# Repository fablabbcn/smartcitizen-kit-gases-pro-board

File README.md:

# Smart Citizen Kit 2.0 Gases Pro Board 

### The core firmware (C++)

The technology used:

* Arduino Zero Core
* Platformio

#### Uploading the firmware to the board

After clonning the repository:

1. In folder ./firmware run:

  * `pio run`

2. This step will **take a while**. Once it finished plug the board over USB and run:

  * `pio run -t upload`

## Documentation

Full documentation under development. Follow the [forum](https://forum.smartcitizen.me/) and [twitter](https://twitter.com/SmartCitizenKit) for updates.

## Related Smart Citizen repositories

* Smart Citizen Kit 2.0 [github.com/fablabbcn/smartcitizen-kit-20](https://github.com/fablabbcn/smartcitizen-kit-20)
* Platform Core API [github.com/fablabbcn/smartcitizen-api](https://github.com/fablabbcn/smartcitizen-api)
* Platform Web [github.com/fablabbcn/smartcitizen-web](https://github.com/fablabbcn/smartcitizen-web)
* Platform Onboarding [github.com/fablabbcn/smartcitizen-onboarding-app](https://github.com/fablabbcn/smartcitizen-onboarding-app)
* Kit Enclosures [github.com/fablabbcn/smartcitizen-enclosures](https://github.com/fablabbcn/smartcitizen-enclosures)
* Useful software resources for communities [github.com/fablabbcn/smartcitizen-toolkit](https://github.com/fablabbcn/smartcitizen-toolkit)

## License

All the software unless stated is released under [GNU GPL v3.0](https://github.com/fablabbcn/smartcitizen-kit-20/blob/master/LICENSE) and the hardware design files under [CERN OHL v1.2](https://github.com/fablabbcn/smartcitizen-kit-20/blob/master/hardware/LICENSE)

## Credits

Smart Citizen Team 2012-18

## Funding

This work has received funding from the European Union's Horizon 2020 research and innovation program under the grant agreement [No. 689954](https://cordis.europa.eu/project/rcn/202639_en.html)

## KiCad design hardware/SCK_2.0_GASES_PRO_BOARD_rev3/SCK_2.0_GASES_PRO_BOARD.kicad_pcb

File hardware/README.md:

Smart Citizen Kit 2.0 PM Board Hardware
=======================================

This folder contains the KiCad design files for the Smart Citizen Kit 2.0 PM Board

## Folders

* **SCK_2.0_GASES_PRO_BOARD_rev3** The SCK Gases Pro Alphasense Driver Board
* **SCK_2.0_GASES_PRO_BOARD_TEST_UTIL_rev2** The SCK Gases Pro Calibration and Test Util

## License

All the software is released under [GNU GPL v3.0](https://github.com/fablabbcn/smartcitizen-kit-20/blob/master/LICENSE) and the hardware design files under [CERN OHL v1.2](https://github.com/fablabbcn/smartcitizen-kit-20/blob/master/hardware/LICENSE)

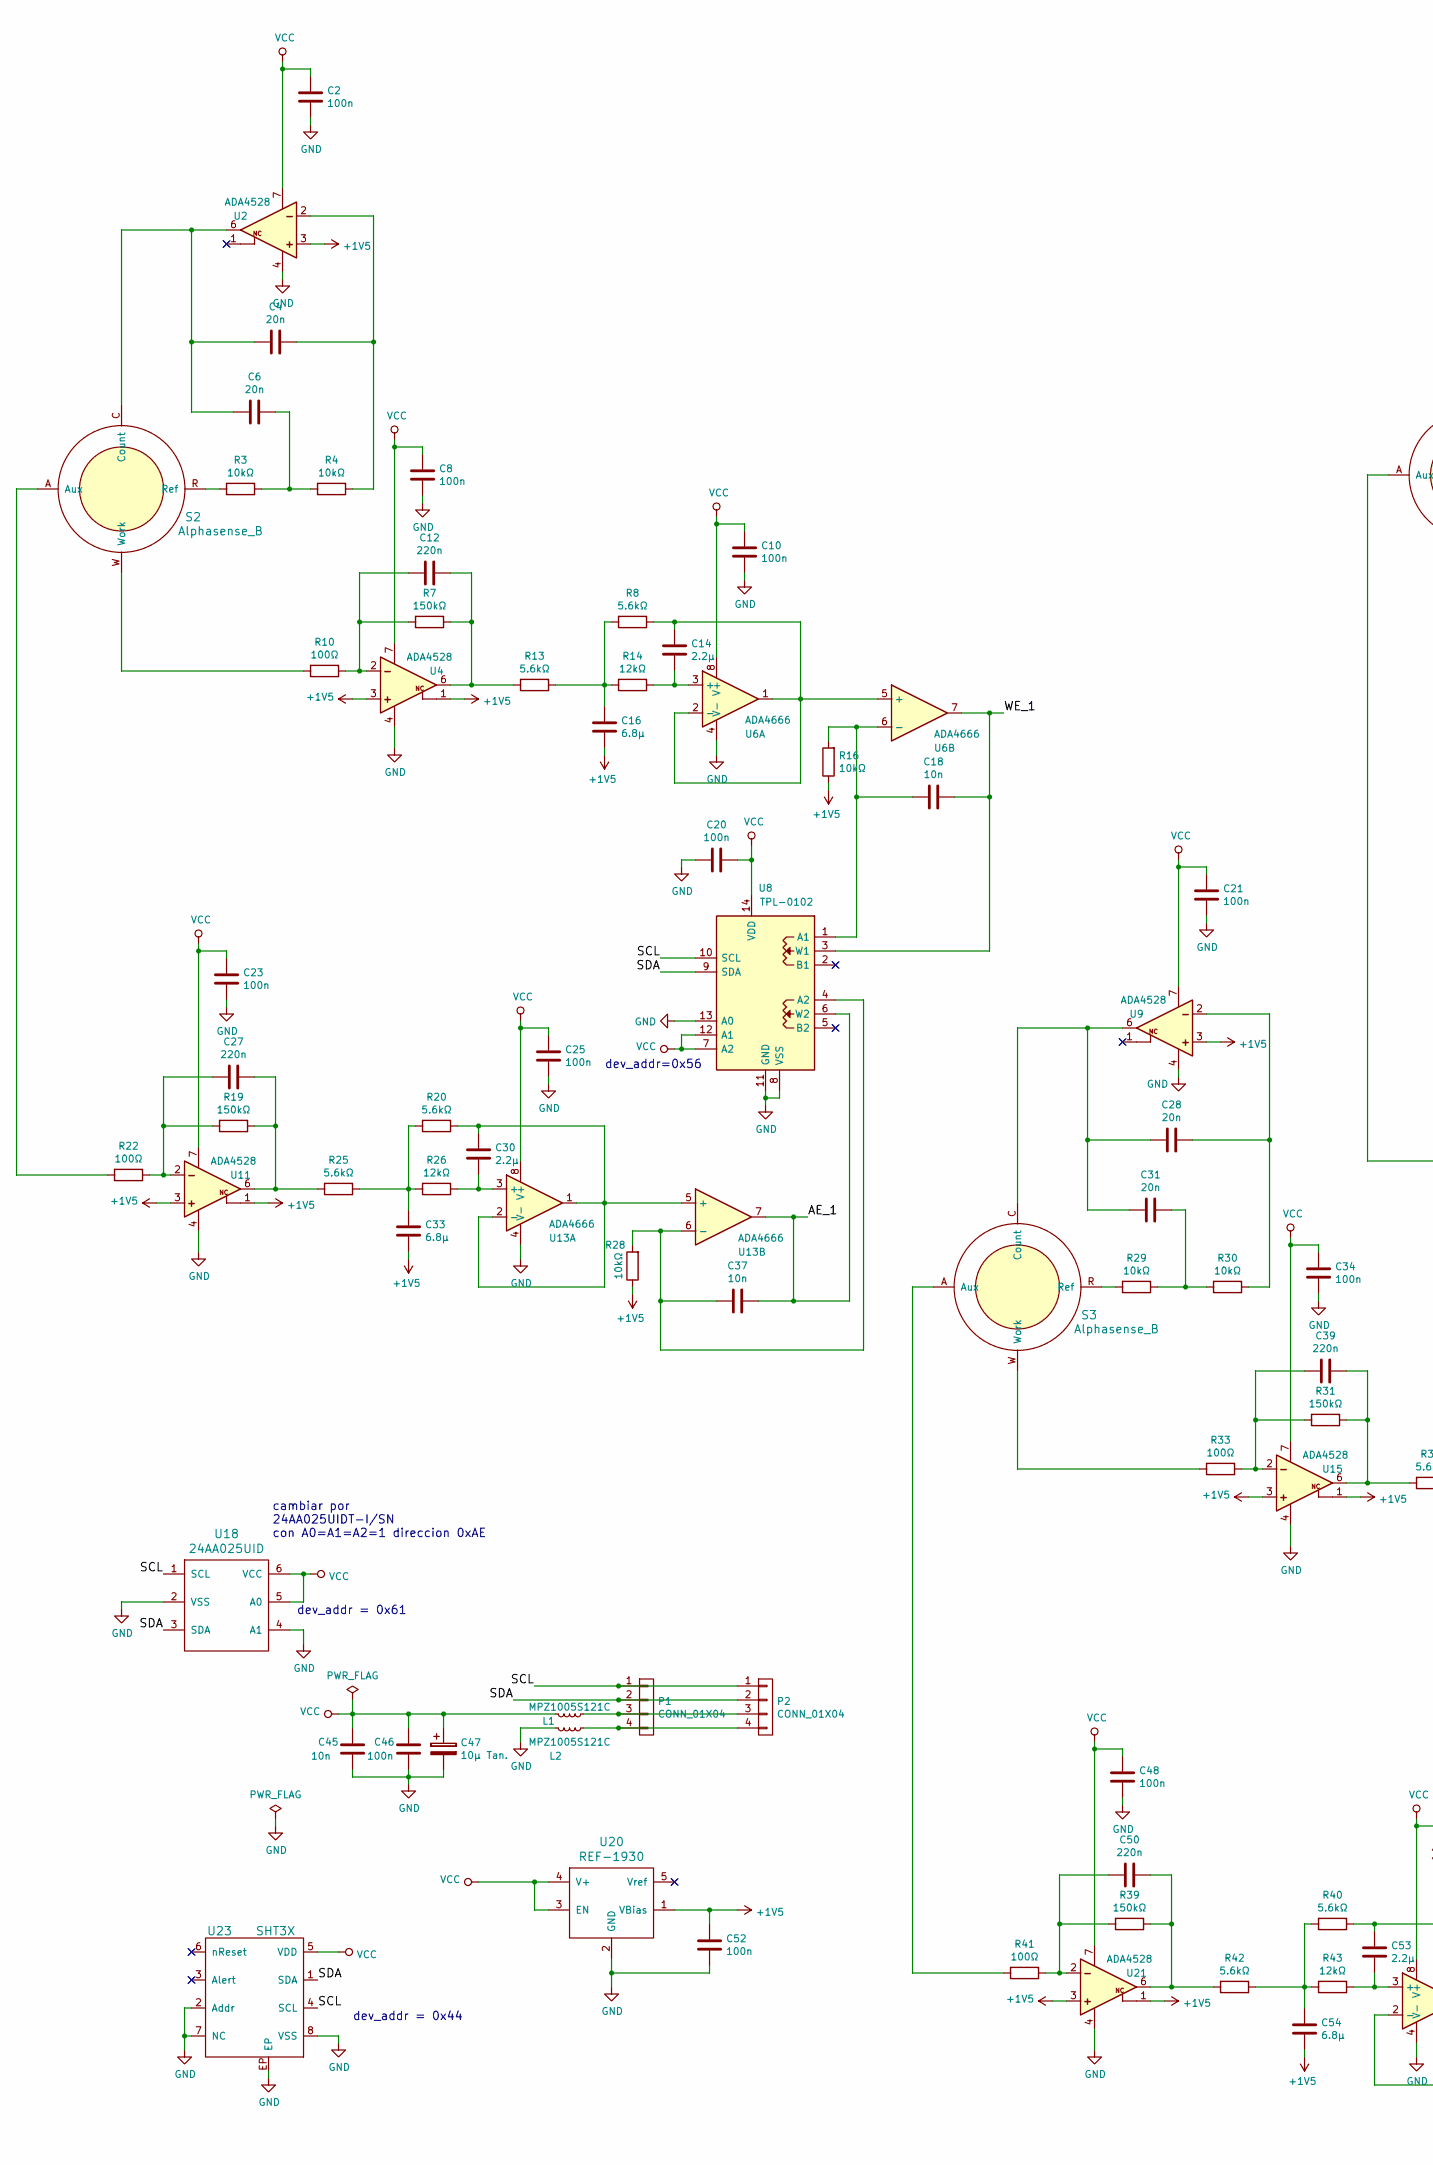
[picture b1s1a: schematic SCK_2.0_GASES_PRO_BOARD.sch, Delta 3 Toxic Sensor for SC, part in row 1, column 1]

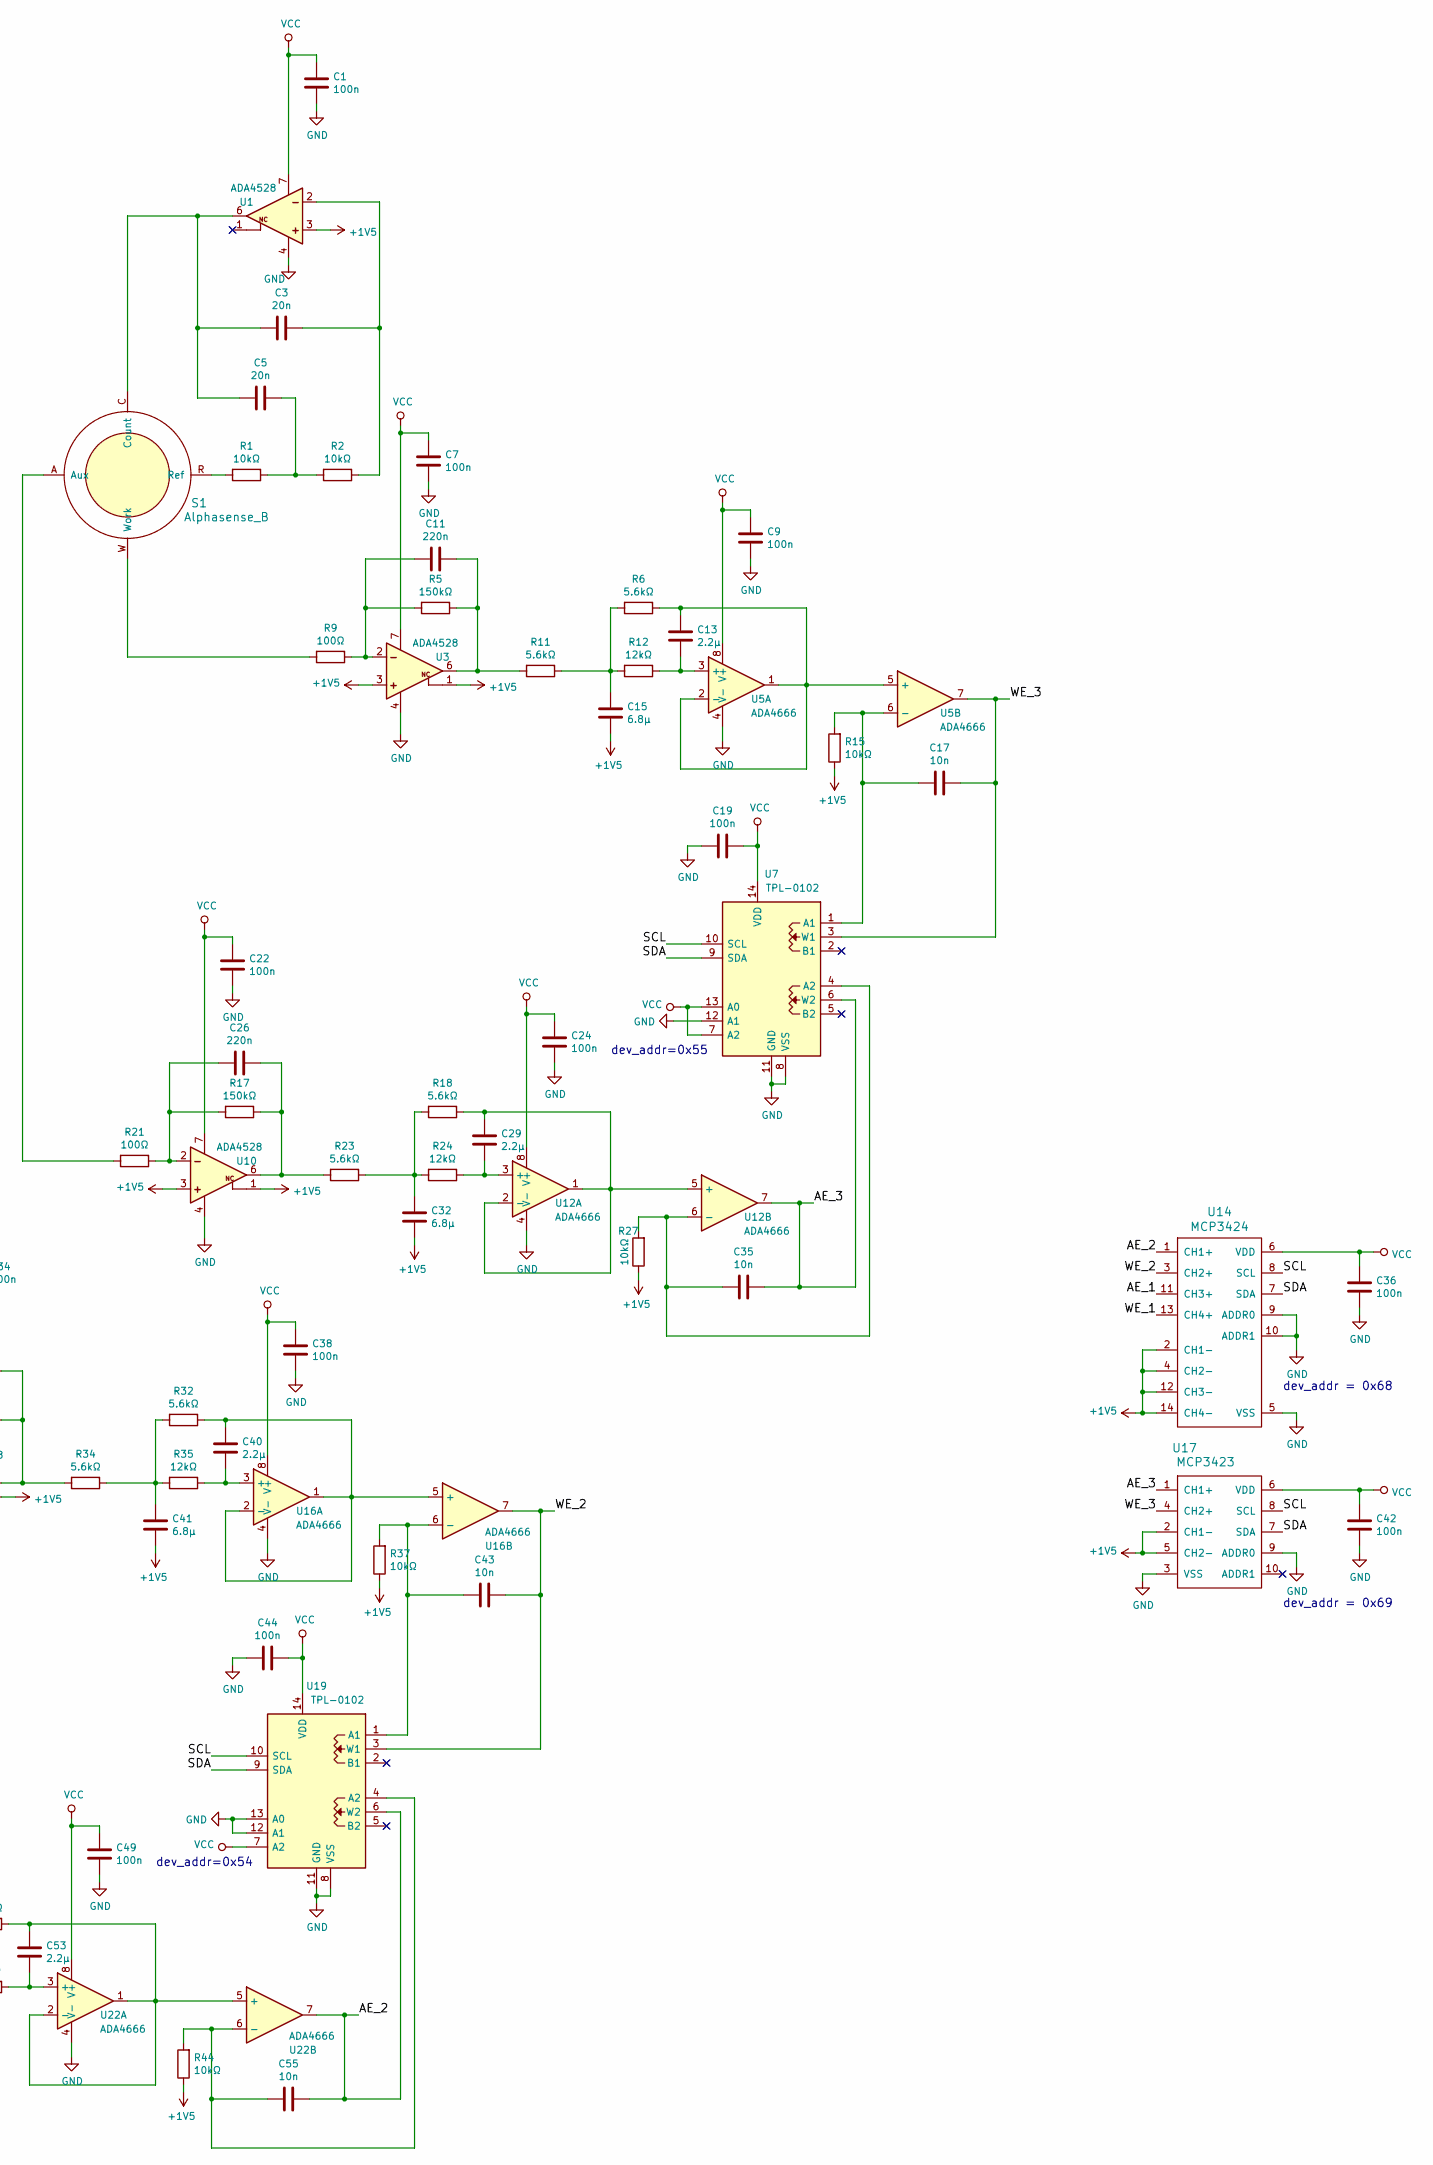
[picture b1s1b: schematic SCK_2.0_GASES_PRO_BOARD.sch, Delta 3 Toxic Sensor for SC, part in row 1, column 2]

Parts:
C1, C2, C7, C8, C9, C10, C19, C20, C21, C22, C23, C24, C25, C34, C36, C38, C42, C44, C46, C48, C49, C52: 100n; C_0603
C3, C4, C5, C6, C28, C31: 20n; C_0603
C11, C12, C26, C27, C39, C50: 220n; C_0603
C13, C14, C29, C30, C40, C53: 2.2µ; C_0603
C15, C16, C32, C33, C41, C54: 6.8µ; C_0603
C17, C18, C35, C37, C43, C45, C55: 10n; C_0603
C47: 10µ Tan.; CP_Tantalum_Case-A_EIA-3216-18_Reflow
L1, L2: MPZ1005S121C; R_0402
P1, P2: CONN_01X04; HW4-SMD-2.0
R1, R2, R3, R4, R15, R16, R27, R28, R29, R30, R37, R44: 10kΩ; R_0603
R5, R7, R17, R19, R31, R39: 150kΩ; R_0603
R6, R8, R11, R13, R18, R20, R23, R25, R32, R34, R40, R42: 5.6kΩ; R_0603
R9, R10, R21, R22, R33, R41: 100Ω; R_0603
R12, R14, R24, R26, R35, R43: 12kΩ; R_0603
S1, S2, S3: Alphasense_B; Alphasense_B-4
U1, U2, U3, U4, U9, U10, U11, U15, U21: ADA4528; MSOP-8_3x3mm_Pitch0.65mm
U5, U6, U12, U13, U16, U22: ADA4666; MSOP-8_3x3mm_Pitch0.65mm
U7, U8, U19: TPL-0102; QFN14(2X2MM)
U14: MCP3424; TSSOP-14_4.4x5mm_Pitch0.65mm
U17: MCP3423; MSOP-10_3x3mm_Pitch0.5mm
U18: 24AA025UID; SOT-23-6
U20: REF-1930; SOT-23-5
U23: SHT3X; DFN-8-1EP_2x2mm_Pitch0.5mm

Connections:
+1V5: C15.1, C16.1, C32.1, C33.1, C41.1, C52.1, C54.1, R15.1, R16.1, R27.1, R28.1, R37.1, R44.1, U1.3 (NOT-INV.INPUT), U2.3 (NOT-INV.INPUT), U3.1 (NC), U3.3 (NOT-INV.INPUT), U4.1 (NC), U4.3 (NOT-INV.INPUT), U9.3 (NOT-INV.INPUT), U10.1 (NC), U10.3 (NOT-INV.INPUT), U11.1 (NC), U11.3 (NOT-INV.INPUT), U14.2 (CH1-), U14.4 (CH2-), U14.12 (CH3-), U14.14 (CH4-), U15.1 (NC), U15.3 (NOT-INV.INPUT), U17.2 (CH1-), U17.5 (CH2-), U20.1 (VBias), U21.1 (NC), U21.3 (NOT-INV.INPUT)
/AE_1: C37.2, U8.6 (W2), U13.7, U14.11 (CH3+)
/AE_2: C55.2, U14.1 (CH1+), U19.6 (W2), U22.7
/AE_3: C35.2, U7.6 (W2), U12.7, U17.1 (CH1+)
/SCL: P1.1, P2.1, U7.10 (SCL), U8.10 (SCL), U14.8 (SCL), U17.8 (SCL), U18.1 (SCL), U19.10 (SCL), U23.4 (SCL)
/SDA: P1.2, P2.2, U7.9 (SDA), U8.9 (SDA), U14.7 (SDA), U17.7 (SDA), U18.3 (SDA), U19.9 (SDA), U23.1 (SDA)
/WE_1: C18.2, U6.7, U8.3 (W1), U14.13 (CH4+)
/WE_2: C43.2, U14.3 (CH2+), U16.7, U19.3 (W1)
/WE_3: C17.2, U5.7, U7.3 (W1), U17.4 (CH2+)
GND: C1.2, C2.2, C7.2, C8.2, C9.2, C10.2, C19.1, C20.1, C21.2, C22.2, C23.2, C24.2, C25.2, C34.2, C36.2, C38.2, C42.2, C44.1, C45.2, C46.2, C47.2, C48.2, C49.2, C52.2, L2.2, U1.4 (V-), U2.4 (V-), U3.4 (V-), U4.4 (V-), U5.4 (V-), U6.4 (V-), U7.8 (VSS), U7.11 (GND), U7.12 (A1), U8.8 (VSS), U8.11 (GND), U8.13 (A0), U9.4 (V-), U10.4 (V-), U11.4 (V-), U12.4 (V-), U13.4 (V-), U14.5 (VSS), U14.9 (ADDR0), U14.10 (ADDR1), U15.4 (V-), U16.4 (V-), U17.3 (VSS), U17.9 (ADDR0), U18.2 (VSS), U18.4 (A1), U19.8 (VSS), U19.11 (GND), U19.12 (A1), U19.13 (A0), U20.2 (GND), U21.4 (V-), U22.4 (V-), U23.2 (Addr), U23.7 (NC), U23.8 (VSS), U23.9, U23.EP
unnamed: C3.1, R2.1, U1.2 (INV.INPUT)
unnamed: C3.2, C5.2, S1.C (Count), U1.6 (OUTPUT)
unnamed: C4.1, R4.1, U2.2 (INV.INPUT)
unnamed: C4.2, C6.2, S2.C (Count), U2.6 (OUTPUT)
unnamed: C5.1, R1.1, R2.2
unnamed: C6.1, R3.1, R4.2
unnamed: C11.1, R5.1, R11.2, U3.6 (OUTPUT)
unnamed: C11.2, R5.2, R9.1, U3.2 (INV.INPUT)
unnamed: C12.1, R7.1, R13.2, U4.6 (OUTPUT)
unnamed: C12.2, R7.2, R10.1, U4.2 (INV.INPUT)
unnamed: C13.1, R12.1, U5.3 (+)
unnamed: C13.2, R6.1, U5.1, U5.2 (-), U5.5 (+)
unnamed: C14.1, R14.1, U6.3 (+)
unnamed: C14.2, R8.1, U6.1, U6.2 (-), U6.5 (+)
unnamed: C15.2, R6.2, R11.1, R12.2
unnamed: C16.2, R8.2, R13.1, R14.2
unnamed: C17.1, R15.2, U5.6 (-), U7.1 (A1)
unnamed: C18.1, R16.2, U6.6 (-), U8.1 (A1)
unnamed: C26.1, R17.1, R23.2, U10.6 (OUTPUT)
unnamed: C26.2, R17.2, R21.1, U10.2 (INV.INPUT)
unnamed: C27.1, R19.1, R25.2, U11.6 (OUTPUT)
unnamed: C27.2, R19.2, R22.1, U11.2 (INV.INPUT)
unnamed: C28.1, R30.1, U9.2 (INV.INPUT)
unnamed: C28.2, C31.2, S3.C (Count), U9.6 (OUTPUT)
unnamed: C29.1, R24.1, U12.3 (+)
unnamed: C29.2, R18.1, U12.1, U12.2 (-), U12.5 (+)
unnamed: C30.1, R26.1, U13.3 (+)
unnamed: C30.2, R20.1, U13.1, U13.2 (-), U13.5 (+)
unnamed: C31.1, R29.1, R30.2
unnamed: C32.2, R18.2, R23.1, R24.2
unnamed: C33.2, R20.2, R25.1, R26.2
unnamed: C35.1, R27.2, U7.4 (A2), U12.6 (-)
unnamed: C37.1, R28.2, U8.4 (A2), U13.6 (-)
unnamed: C39.1, R31.1, R34.2, U15.6 (OUTPUT)
unnamed: C39.2, R31.2, R33.1, U15.2 (INV.INPUT)
unnamed: C40.1, R35.1, U16.3 (+)
unnamed: C40.2, R32.1, U16.1, U16.2 (-), U16.5 (+)
unnamed: C41.2, R32.2, R34.1, R35.2
unnamed: C43.1, R37.2, U16.6 (-), U19.1 (A1)
unnamed: C50.1, R39.1, R42.2, U21.6 (OUTPUT)
unnamed: C50.2, R39.2, R41.1, U21.2 (INV.INPUT)
unnamed: C53.1, R43.1, U22.3 (+)
unnamed: C53.2, R40.1, U22.1, U22.2 (-), U22.5 (+)
unnamed: C54.2, R40.2, R42.1, R43.2
unnamed: C55.1, R44.2, U19.4 (A2), U22.6 (-)
unnamed: L1.1, P1.3, P2.3
unnamed: L2.1, P1.4, P2.4
unnamed: R1.2, S1.R (Ref)
unnamed: R3.2, S2.R (Ref)
unnamed: R9.2, S1.W (Work)
unnamed: R10.2, S2.W (Work)
unnamed: R21.2, S1.A (Aux)
unnamed: R22.2, S2.A (Aux)
unnamed: R29.2, S3.R (Ref)
unnamed: R33.2, S3.W (Work)
unnamed: R41.2, S3.A (Aux)
VCC: C1.1, C2.1, C7.1, C8.1, C9.1, C10.1, C19.2, C20.2, C21.1, C22.1, C23.1, C24.1, C25.1, C34.1, C36.1, C38.1, C42.1, C44.2, C45.1, C46.1, C47.1, C48.1, C49.1, L1.2, U1.7 (V+), U2.7 (V+), U3.7 (V+), U4.7 (V+), U5.8 (V+), U6.8 (V+), U7.7 (A2), U7.13 (A0), U7.14 (VDD), U8.7 (A2), U8.12 (A1), U8.14 (VDD), U9.7 (V+), U10.7 (V+), U11.7 (V+), U12.8 (V+), U13.8 (V+), U14.6 (VDD), U15.7 (V+), U16.8 (V+), U17.6 (VDD), U18.5 (A0), U18.6 (VCC), U19.7 (A2), U19.14 (VDD), U20.3 (EN), U20.4 (V+), U21.7 (V+), U22.8 (V+), U23.5 (VDD)

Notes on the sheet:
dev_addr=0x56
dev_addr=0x54
dev_addr=0x55
dev_addr = 0x61
dev_addr = 0x69
dev_addr = 0x68
dev_addr = 0x44
cambiar por 24AA025UIDT-I/SN con A0=A1=A2=1 direccion 0xAE

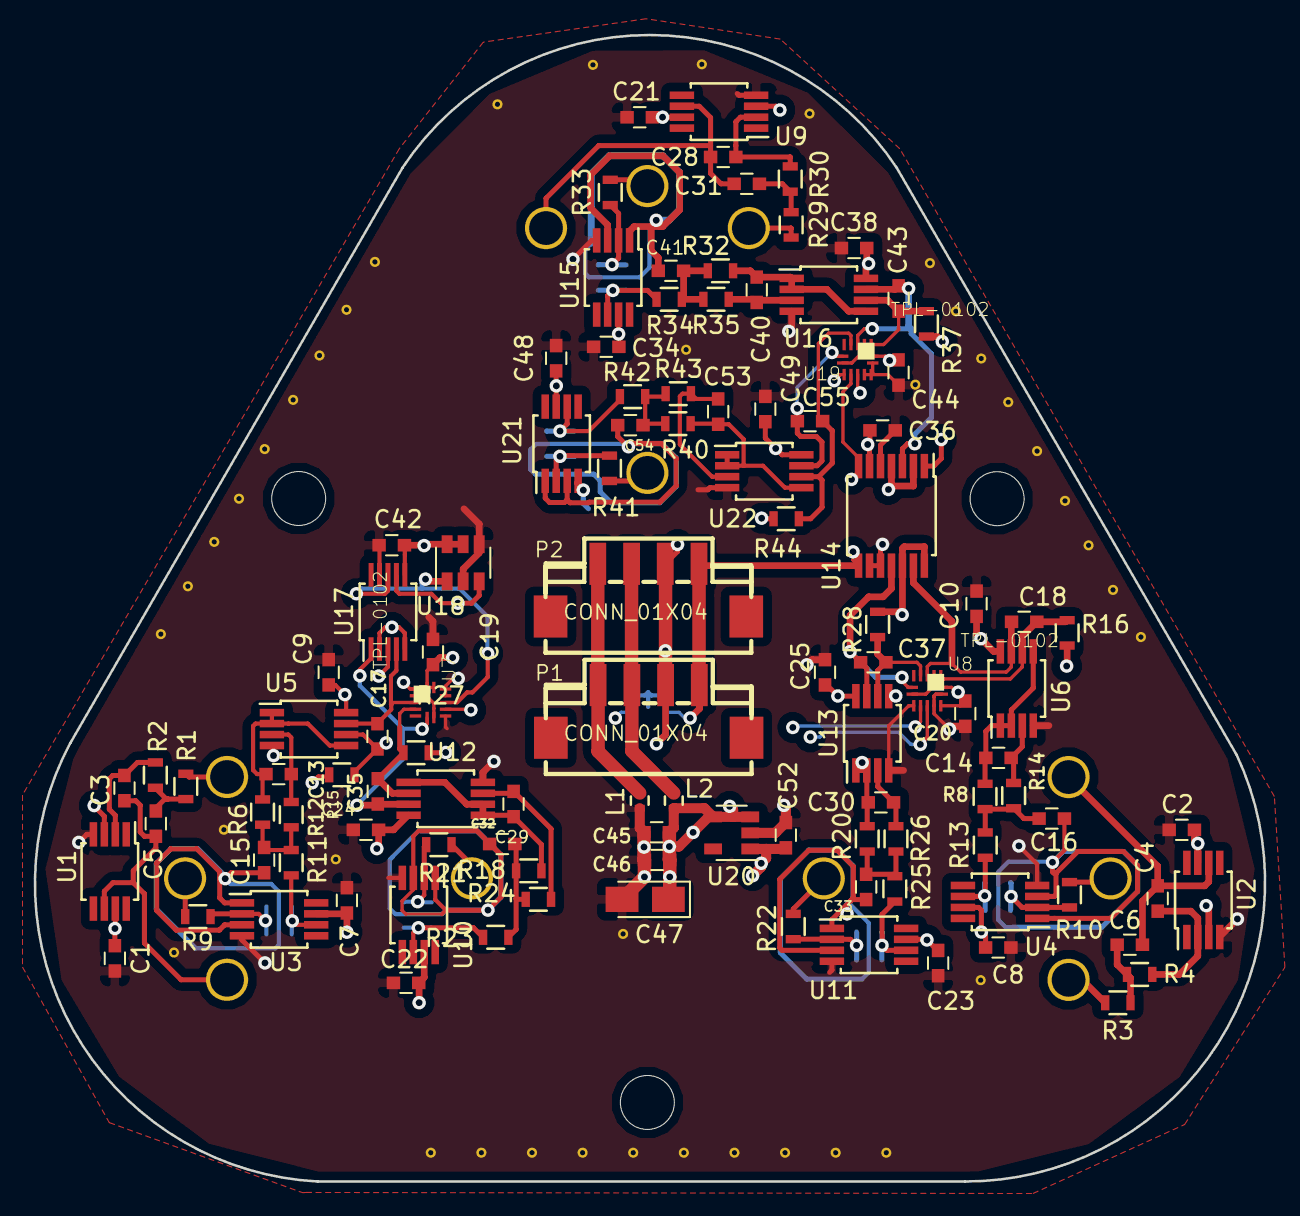
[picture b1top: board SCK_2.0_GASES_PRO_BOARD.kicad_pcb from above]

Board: 4 copper layers, 72.9 x 68.0 mm, 126 parts (0 on the bottom side), 67 nets.

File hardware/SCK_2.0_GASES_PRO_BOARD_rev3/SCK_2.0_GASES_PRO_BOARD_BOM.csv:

Id,Designator,Package,Quantity,Designation,Manufacturer,Manufacturer Part Number,Description,Mouser Part Number,Mouser Alternative Part Number,Mouser Stock,Digikey Part Number,Digikey Stock,Seeedstudio Part Number ,Seeedstudio Stock
,,,,,,,,,,,,,,
1,"U7,U8,U19",QFN14(2X2MM),3,TPL-0102,Texas Instruments,TPL0102-100RUCR,Digital Potentiometer ICs Digital Potentiometer ICs 256 Taps Dual Ch Digital Pot,595-TPL0102-100RUCR,,,296-28379-1-ND,,,
4,"U2,U1,U3,U4,U9,U10,U11,U15,U21",MSOP-8_3x3mm_Pitch0.65mm,9,ADA4528-1,Analog Devices Inc.,ADA4528-1ARMZ,Precision Amplifiers Precision Amplifiers 5V Ultralow Noise Zero-Drift RRIO Dual,584-ADA4528-1ARMZ,,,ADA4528-1ARMZ-R7CT-ND,,,
6,"U6,U5,U12,U13,U16,U22",MSOP-8_3x3mm_Pitch0.65mm,6,ADA4528-2,Analog Devices Inc.,ADA4528-2ARMZ,Precision Amplifiers Precision Amplifiers 18V LowPower RRIO Untrimmed CmosAmp,584-ADA4528-2ARMZ,,,ADA4528-2ARMZ-R7CT-ND,,,
21,U14,TSSOP-14_4.4x5mm_Pitch0.65mm,1,MCP3424,Microchip,MCP3424-E/ST,Analog to Digital Converters - ADC Analog to Digital Converters - ADC 18B delta-sigma ADC dual Ch 4sps,579-MCP3424-E/ST,,,MCP3424-E/ST-ND,,,
22,U18,SOT-23-6,1,24AA025UID,Microchip,24AA025UIDT-I/OT,EEPROM EEPROM 2K I2C EE Unique ID,579-24AA025UIDT-I/OT,,,24AA025UIDT-I/OTCT-ND,,,
23,U20,SOT-23-5,1,REF-1930,Texas Instruments,REF1930AIDDCT,Voltage References Voltage References Dual Output Vref & Vref/2 Voltage Ref,595-REF1930AIDDCT,,,296-38443-1-ND,,,
24,U23,DFN-6-1EP_3x3mm_Pitch0.95mm,1,SHT31,Sensirion,SHT31-DIS-B,Board Mount Humidity Sensors Board Mount Humidity Sensors +/- 2%RH 8-PIN DFN pkg,403-SHT31-DIS-F,,,1649-1066-1-ND,,,
25,U17,MSOP-10_3x3mm_Pitch0.5mm,1,MCP3423,Microchip,MCP3423-E/UN,Analog to Digital Converters - ADC 18B delta-sigma ADC dual Ch 4sps,579-MCP3423-E/UN,,,MCP3423-E/UN-ND,,,
,,,,,,,,,,,,,,
3,"S3,S2,S1",Alphasense_B-4,12,Alphasense_B_Conector,Harwin,H3183-01,Circuit Board Hardware - PCB Circuit Board Hardware - PCB 1mm PC BOARD SOCKET TIN,855-H3183-01,,,952-1468-ND,,,
8,"P2,P1",HW4-SMD-2.0,2,CONN_01X04,Seedstudio,CONN_01X04,1125S-SMT-4P ,,,,,,320110030,
,,,,,,,,,,,,,,
15,"L1,L2",R_0402,2,MPZ1005S121C,TDK,MPZ1005S121C,"Ferrite Beads Ferrite Beads 120ohms, 1.2A 0.09ohms",810-MPZ1005S121C,,,,,,
,,,,,,,,,,,,,,
5,"C20,C1,C2,C7,C8,C9,C10,C19,C21,C22,C23,C24,C25,C34,C36,C38,C42,C44,C46,C48,C49,C52",C_0603,22,100n,AVX,06033C104K4T2A,Multilayer Ceramic Capacitors MLCC - SMD/SMT 25V .1uF X7R 0603 10% Tol,581-06033C104K4,,,,,,
9,"C3,C4,C5,C6,C28,C31",C_0603,6,20n,AVX,0603ZC223JAT2A,Multilayer Ceramic Capacitors MLCC - SMD/SMT Multilayer Ceramic Capacitors MLCC - SMD/SMT 10V .022uF X7R 0603 5% Tol,581-0603ZC223JAT2A,710-885012206042,,0603ZC223JAT2A-ND,,,
10,"C11,C12,C26,C27,C39,C50",C_0603,6,220n,AVX,0603ZC224JAT2A,Multilayer Ceramic Capacitors MLCC - SMD/SMT Multilayer Ceramic Capacitors MLCC - SMD/SMT 10V .22uF X7R 0603 5% Tol,581-0603ZC224J,,,478-6035-1-ND,,,
11,"C13,C14,C29,C30,C40,C53",C_0603,6,2.2µ,AVX,0603ZC225KAT2A,Multilayer Ceramic Capacitors MLCC - SMD/SMT Multilayer Ceramic Capacitors MLCC - SMD/SMT 10V 2.2uF X7R 0603 10% Tol,581-0603ZC225KAT2A,,,,,,
12,"C15,C16,C32,C33,C41,C54",C_0603,6,6.8µ,TDK,C1608X5R1A685K080AC,Multilayer Ceramic Capacitors MLCC - SMD/SMT Multilayer Ceramic Capacitors MLCC - SMD/SMT 0805 6.8uF 10volts X7R 10%,810-C2012X7R1A685K1C,,,445-14529-1-ND,,,
13,"C17,C18,C35,C37,C43,C45,C55",C_0603,7,10n,AVX,0603ZC103JAT2A,Multilayer Ceramic Capacitors MLCC - SMD/SMT Multilayer Ceramic Capacitors MLCC - SMD/SMT 10V .01uF X7R 0603 5% Tol,581-0603ZC103J,,,0603ZC103JAT2A-ND,,,
14,C47,CP_Tantalum_Case-A_EIA-3216-18_Reflow,1,10µ Tan.,AVX,TRJA106K010R1800,Tantalum Capacitors - Solid SMD Tantalum Capacitors - Solid SMD 10uF +/-10% 10V ESR=1800,581-TRJA106K010R1800,,,,,,
,,,,,,,,,,,,,,
16,"R1,R2,R3,R4,R15,R16,R27,R28,R29,R30,R37,R44",R_0603,12,10kΩ,Vishay,MCT06030C1002FP500,Thin Film Resistors - SMD Thin Film Resistors - SMD .1W 10Kohms 1% 0603 50ppm Auto,594-MCT06030C1002FP5,,,MCT0603-10.0K-CFCT-ND,,,
17,"R5,R7,R17,R19,R31,R39",R_0603,6,150kΩ,Vishay,MCT06030C1503FP500,Thin Film Resistors - SMD Thin Film Resistors - SMD .1W 150Kohm 1% 0603 50ppm Auto,594-MCT06030C1503FP5,,,MCT0603-150K-CFCT-ND,,,
18,"R6,R8,R11,R13,R18,R20,R23,R25,R32,R34,R40,R42",R_0603,12,5.6kΩ,Vishay,MCT06030C5601FP500,Thin Film Resistors - SMD Thin Film Resistors - SMD .1W 5.6Kohm 1% 0603 50ppm Auto,594-MCT06030C5601FP5,,,MCT0603-5.60K-CFCT-ND,,,
19,"R9,R10,R21,R22,R33,R41",R_0603,6,100Ω,Vishay,MCT06030C1000FP500,Thin Film Resistors - SMD Thin Film Resistors - SMD .1W 100ohm 1% 0603 50ppm Auto,594-MCT06030C1000FP5,,,MCT0603-100-CFCT-ND,,,
20,"R12,R14,R24,R26,R35,R43",R_0603,6,12kΩ,Vishay,MCT06030C1202FP500,Thin Film Resistors - SMD Thin Film Resistors - SMD .1W 12Kohm 1% 0603 50ppm Auto,594-MCT06030C1202FP5,,,MCT0603-12.0K-CFCT-ND,,,
,,,,,,,,,,,,,,
,,,,,,,,,,,,,,
,*All resistor Thin metal film,,,,,,,,,,,,,
,All capacitor MMLC X7R (except tantalum),,,,,,,,,,,,,

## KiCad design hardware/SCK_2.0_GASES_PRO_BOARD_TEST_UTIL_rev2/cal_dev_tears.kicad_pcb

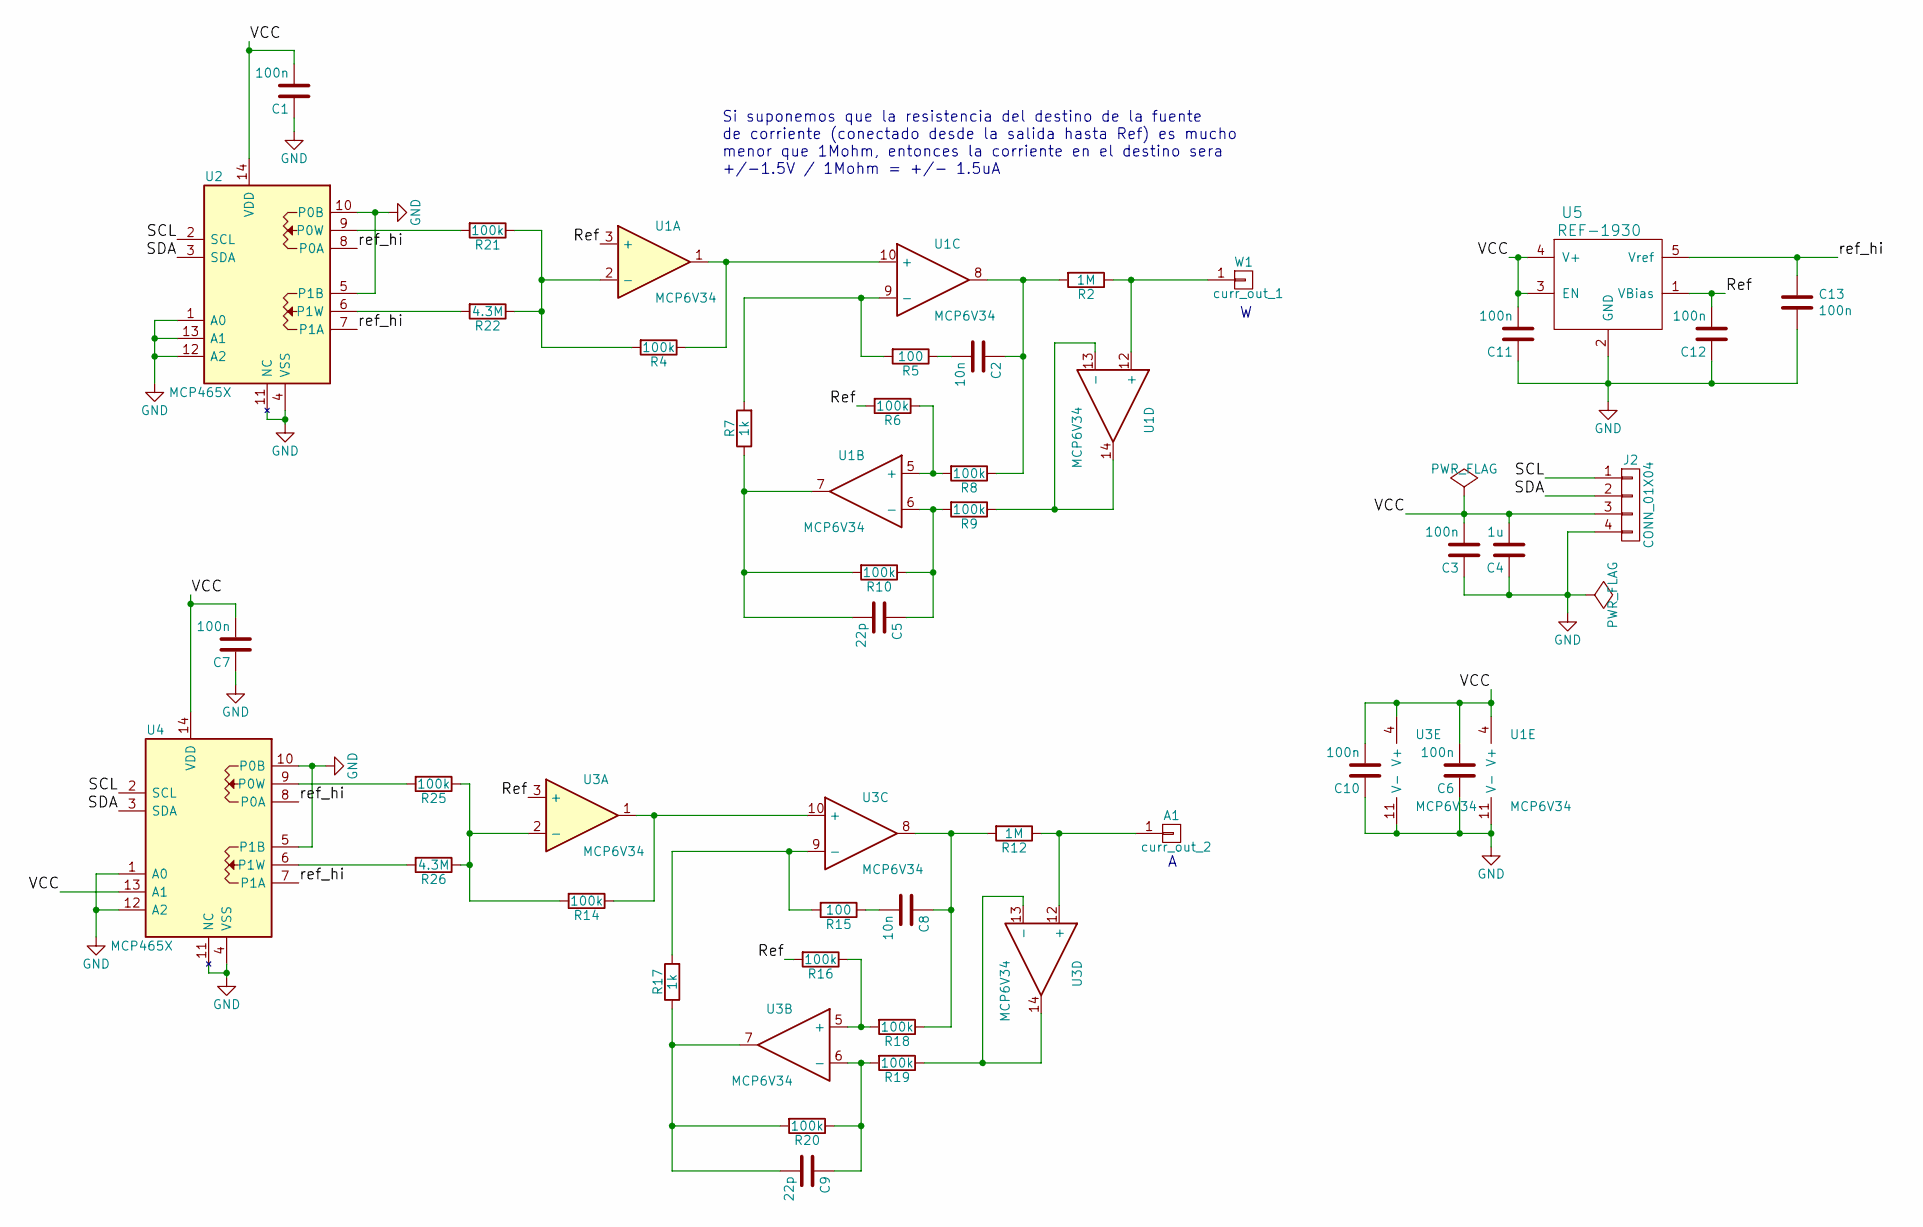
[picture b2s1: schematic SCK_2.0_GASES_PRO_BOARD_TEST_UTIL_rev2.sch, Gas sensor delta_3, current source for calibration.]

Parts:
A1: curr_out_2; 1pin
C1, C3, C6, C7, C10, C11, C12, C13: 100n; C_0603_HandSoldering
C2, C8: 10n; C_0603_HandSoldering
C4: 1u; C_0603_HandSoldering
C5, C9: 22p; C_0603_HandSoldering
J2: CONN_01X04; HW4-SMD-2.0
R2, R12: 1M; R_0805_HandSoldering
R4, R6, R8, R9, R10, R14, R16, R18, R19, R20, R21, R25: 100k; R_0603_HandSoldering
R5, R15: 100; R_0603_HandSoldering
R7, R17: 1k; R_0603_HandSoldering
R22, R26: 4.3M; R_0603_HandSoldering
U1, U3: MCP6V34; TSSOP-14_4.4x5mm_Pitch0.65mm
U2, U4: MCP465X; TSSOP-14_4.4x5mm_Pitch0.65mm
U5: REF-1930; SOT-23-5
W1: curr_out_1; 1pin

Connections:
/Ref: C12.2, R6.2, R16.2, U1.3 (+), U3.3 (+), U5.1 (VBias)
/SCL: J2.1, U2.2 (SCL), U4.2 (SCL); also elsewhere on the board
/SDA: J2.2, U2.3 (SDA), U4.3 (SDA); also elsewhere on the board
/VCC: C1.2, C3.2, C4.2, C6.2, C7.2, C10.2, C11.2, J2.3, U1.4 (V+), U2.14 (VDD), U3.4 (V+), U4.13 (A1), U4.14 (VDD), U5.3 (EN), U5.4 (V+); also elsewhere on the board
/ref_hi: C13.2, U2.7 (P1A), U2.8 (P0A), U4.7 (P1A), U4.8 (P0A), U5.5 (Vref)
GND: C1.1, C3.1, C4.1, C6.1, C7.1, C10.1, C11.1, C12.1, C13.1, J2.4, U1.11 (V-), U2.1 (A0), U2.4 (VSS), U2.5 (P1B), U2.10 (P0B), U2.11 (NC), U2.12 (A2), U2.13 (A1), U3.11 (V-), U4.1 (A0), U4.4 (VSS), U4.5 (P1B), U4.10 (P0B), U4.11 (NC), U4.12 (A2), U5.2 (GND); also elsewhere on the board
unnamed: C2.1, R2.2, R8.1, U1.8
unnamed: C2.2, R5.1
unnamed: C5.1, R9.2, R10.1, U1.6 (-)
unnamed: C5.2, R7.1, R10.2, U1.7
unnamed: C8.1, R12.2, R18.1, U3.8
unnamed: C8.2, R15.1
unnamed: C9.1, R19.2, R20.1, U3.6 (-)
unnamed: C9.2, R17.1, R20.2, U3.7
unnamed 14: R2.1, U1.12 (+), W1.1; also elsewhere on the board
unnamed 15: A1.1, R12.1, U3.12 (+); also elsewhere on the board
unnamed: R4.1, U1.1, U1.10 (+)
unnamed: R5.2, R7.2, U1.9 (-)
unnamed: R6.1, R8.2, U1.5 (+)
unnamed: R9.1, U1.13 (-), U1.14
unnamed: R14.1, U3.1, U3.10 (+)
unnamed: R14.2, R25.1, R26.1, U3.2 (-)
unnamed: R15.2, R17.2, U3.9 (-)
unnamed: R16.1, R18.2, U3.5 (+)
unnamed: R19.1, U3.13 (-), U3.14
unnamed: R4.2, R21.1, R22.1, U1.2 (-)
unnamed: R21.2, U2.9 (P0W)
unnamed: R22.2, U2.6 (P1W)
unnamed: R25.2, U4.9 (P0W)
unnamed: R26.2, U4.6 (P1W)

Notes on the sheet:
Si suponemos que la resistencia del destino de la fuente de corriente (conectado desde la salida hasta Ref) es mucho menor que 1Mohm, entonces la corriente en el destino sera +/-1.5V / 1Mohm = +/- 1.5uA

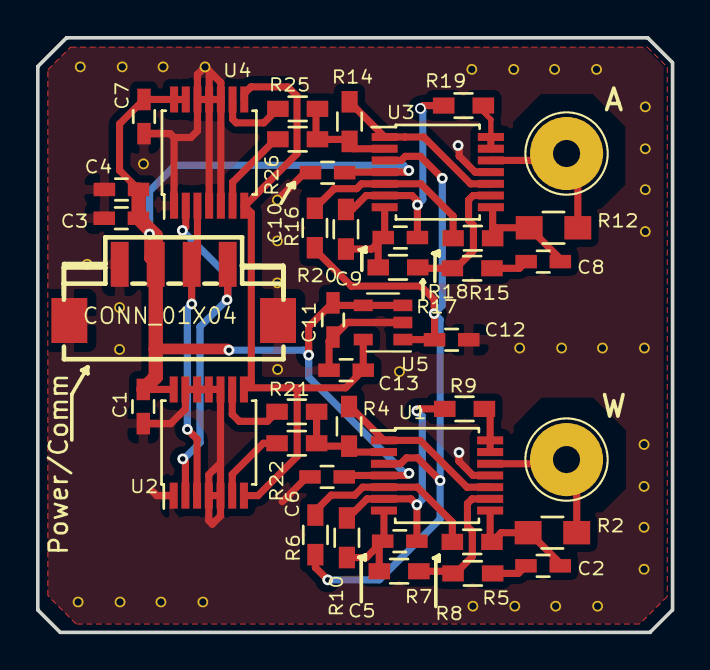
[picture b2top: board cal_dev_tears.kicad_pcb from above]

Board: 2 copper layers, 35.3 x 33.0 mm, 41 parts (0 on the bottom side), 30 nets.

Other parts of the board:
A: curr_out_2; 1pin
Power/Comm: CONN_01X04; HW4-SMD-2.0
W: curr_out_1; 1pin

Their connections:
/SCL: Power/Comm.1; also elsewhere on the board
/SDA: Power/Comm.2; also elsewhere on the board
/VCC: Power/Comm.3; also elsewhere on the board
GND: Power/Comm.4, Power/Comm.SS1, Power/Comm.SS2; also elsewhere on the board
unnamed 14: W.1; also elsewhere on the board
unnamed 15: A.1; also elsewhere on the board

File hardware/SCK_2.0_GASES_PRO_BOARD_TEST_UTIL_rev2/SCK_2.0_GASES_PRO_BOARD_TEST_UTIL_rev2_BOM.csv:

Id,Designator,Package,Quantity,Designation,Manufacturer Part Number,Description,Mouser Part Number,Mouser Alternative Part Number,Mouser Stock,Digikey Part Number,Digikey Stock,Seeedstudio Part Number ,Seeedstudio Stock
2,"U3,U1",TSSOP-14_4.4x5mm_Pitch0.65mm,2,MCP6V34-E/ST,,,,,,,,,
3,"U4,U2",TSSOP-14_4.4x5mm_Pitch0.65mm,2,MCP4651-103/ST,,Digital pot. 10K,579-MCP4651-103/ST,,,,,,
4,A,1pin,1,curr_out_2,Keystone,,534-1402-3,,,,,,
5,W,1pin,1,curr_out_1,Keystone,,534-1402-3,,,,,,
6,Power/Comm,HW4-SMD-2.0,1,CONN_01X04,,1125S-SMT-4P ,,,,,,320110030,
7,U5,SOT-23-5,1,REF-1930,Texas Instruments,REF1930AIDDCT,Voltage References Voltage References Dual Output Vref & Vref/2 Voltage Ref,595-REF1930AIDDCT,,Yes,296-38443-1-ND,Yes,
8,"C1,C3,C6,C7,C10,C11,C12,C13",C_0603_HandSoldering,8,100n,,,,,,,,,
9,"C2,C8",C_0603_HandSoldering,2,10n,,,,,,,,,
10,C4,C_0603_HandSoldering,1,1u,,,,,,,,,
11,"C5,C9",C_0603_HandSoldering,2,22p,,,,,,,,,
12,"R2,R12",R_0805_HandSoldering,2,1M 0.5%,,,,,,,,,
13,"R4,R6,R8,R9,R10,R14,R16,R18,R19,R20,R21,R25",R_0603_HandSoldering,12,100k 0.5% o 0.1%,,,,,,,,,
14,"R5,R15",R_0603_HandSoldering,2,100,,,,,,,,,
15,"R7,R17",R_0603_HandSoldering,2,1k,,,,,,,,,
16,"R22,R26",R_0603_HandSoldering,2,4.3M,,,,,,,,,
,,,,,,,,,,,,,
,All resistors metal film,,,,,,,,,,,,
,All capacitors X7R or C0G,,,,,,,,,,,,

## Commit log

2018-07-03 First release
2018-07-20 Gases board as a separate library
2018-07-20 Completed lib separation process
2018-07-20 No tester support as default to avoid overhead
2018-07-20 Fix on ADC declaration not passing right Wire interface
2018-07-23 Support for SCK 2.0 separated I2C interface
2018-07-27 Adapted library to new naming -> Start instead of begin
2018-08-21 Adds images
2019-02-14 Updates BOM
2019-02-15 Adds DOI for publication reference
2020-09-04 Added missing libraries
2021-04-16 Remove invalid Icon file
2021-04-16 Remove yet another Icon file
